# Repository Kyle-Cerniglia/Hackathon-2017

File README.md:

# Hackathon-2017

Planning sites:

Here

Trello: https://trello.com/invite/b/pC7O8N0E/f5c4491007a17cb59d3c38045b86c0f3/hackathon-2017

Ground robot that man map a room/navigate it and can respond to a sound and travel to it

Curret robot:

Current plan:
1: Mapping
2: Routing
3: Sound detection
4: Navigation

Sections:

Mobility (Kyle)

Local area data aquisition (Kyle)

Map making

Route plotting (Kinsleigh)

IMU maths (Matthew)

Audio triangulation (Alex)

PCB Design (Eaglecad)
  
Future drone implementation

Parts ordering:

IMU https://www.pololu.com/product/2738

PCB UA center? or http://www.pcbway.com/?ngaw=33&gclid=CMSSk_mwoMsCFQYuaQodDaUIHg

Microphone at RadioShack? https://www.pololu.com/file/0J294/Amplified-Mic-v10.pdf

Sites:

https://www.pololu.com/

http://www.digikey.com/

https://www.sparkfun.com/

http://www.atmel.com/

http://www.pcbway.com/?ngaw=33&gclid=CMSSk_mwoMsCFQYuaQodDaUIHg

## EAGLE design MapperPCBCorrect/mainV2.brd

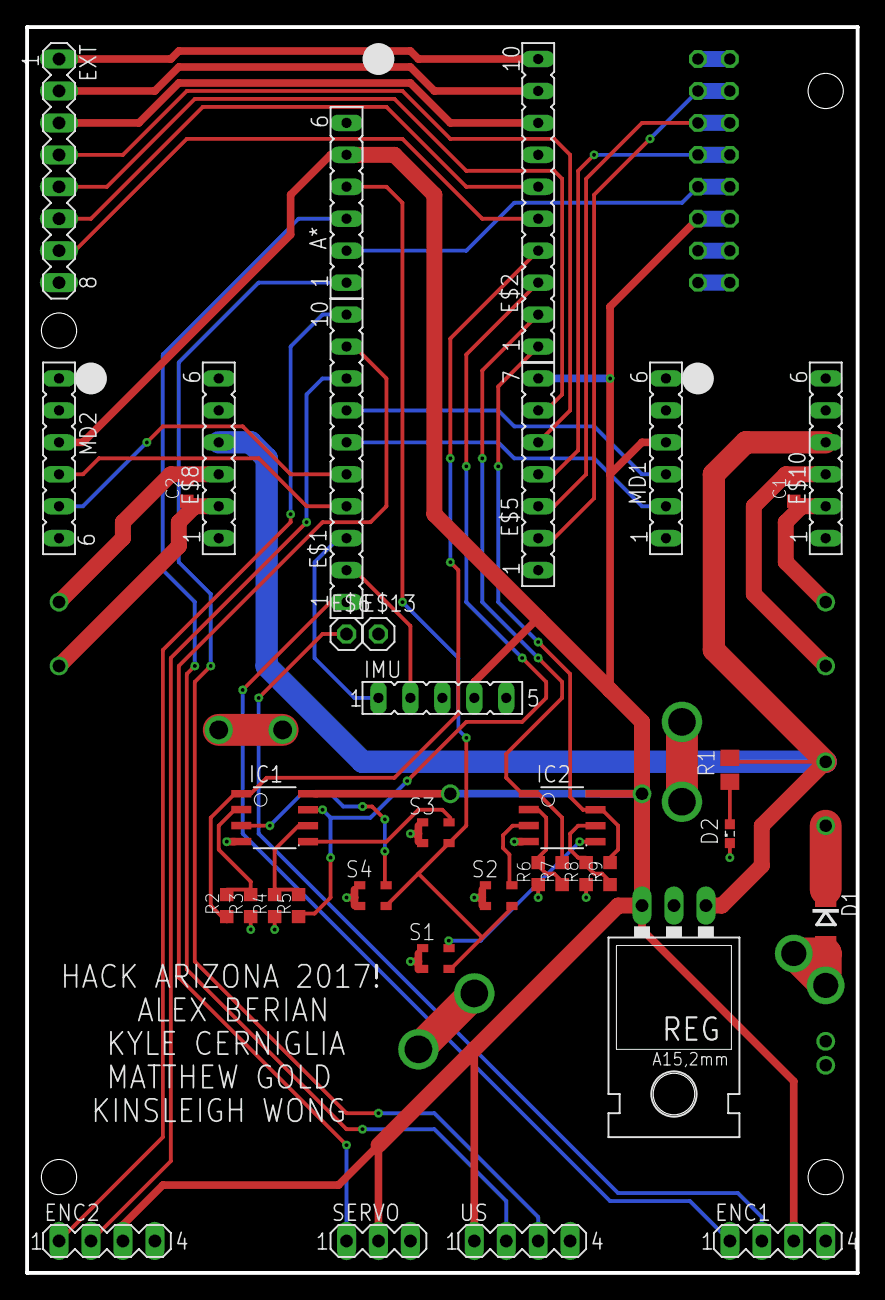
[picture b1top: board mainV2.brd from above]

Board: 2 copper layers, 66.0 x 99.1 mm, 37 parts (1 on the bottom side), 24 nets.

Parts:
A*: FE06
C1, C2: C0603K
D1: DO214AC
D2: SML0603
E$1, E$2: FE10
E$5: FE07
E$6, E$13: 1X01
E$8, E$10: FE06
ENC1, ENC2: MA04-1
EXT: MA08-1
IC1, IC2: 8S1
IMU: FE05-1
MD1, MD2: FE06
R1: R0805
R2, R3, R4, R5, R6, R7, R8, R9: C0603K
REG: TO220L1
S1, S2, S3, S4: ASE
SD: FE08-2
SERVO: MA03-1
US: MA04-1

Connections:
EN1A: E$1.1, ENC1.1
EN2A: E$1.10, ENC2.1
EN2B: E$1.8, ENC2.2
GND: A*.6, E$2.7, E$8.1, E$10.1, ENC1.4, ENC2.4, EXT.8, IMU.3, MD1.1, MD2.6, REG.2, SD.1, SD.2, SD.15, SD.16, SERVO.3, US.4
M1D: E$1.7, MD1.3
M1S: E$1.5, E$1.6, MD1.2, MD2.5
M2D: E$1.4, MD2.4
MISO: E$5.2, SD.3, SD.4
MOSI: E$5.3, SD.5, SD.6
PB0: E$5.5, EXT.4
PD5: E$5.6, EXT.5
PF6: E$2.5, EXT.7
PF7: E$2.6, EXT.6
POW: E$8.4, E$10.4, REG.1
S$1: E$2.9, EXT.2
S$3: E$2.10, EXT.1
S$10: SD.13, SD.14
SCK: E$5.4, SD.7, SD.8
SCL: E$1.3, IMU.1
SDA: E$1.2, IMU.2
SDCS: A*.2, SD.9, SD.10
SERVO: E$1.9, SERVO.1
VCC: A*.5, E$5.7, ENC1.3, ENC2.3, IMU.4, MD1.4, MD2.3, REG.3, SD.11, SD.12, SERVO.2, US.1
VIN: E$2.8, EXT.3

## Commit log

2017-01-07 I added a folder and blank file for me to write the imu stuff to
2017-01-12 I made a test based on the sample provided from imu, it prints to console, it should print the proper acceleration. Kyle please test
2017-01-12 i forgot to save before commiting
2017-01-14 fixed the imu stuff
2017-01-14 dont worry about it
2017-01-14 imu now works it gives speed and degrees turned, it writes that data to the sd card if you divide the speed by .1 you will get displacement
2017-01-15 Add files via upload
    algorithm to load map and traverse to final destination
2017-01-15 Rename main.cpp to algorithm.cpp
2017-01-15 bunch of shit
2018-01-13 myo control
